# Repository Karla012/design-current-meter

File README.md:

# Diseño de un Sistema de Medición de Corriente para Microcontroladores con Transmisión Inalámbrica

### Autores
- **Karla Vanessa Ruíz González** — Universidad Industrial de Santander  
- **Óscar Andrés Meza Ortiz** — Universidad Industrial de Santander  

---

## Descripción del Proyecto

Este proyecto tiene como objetivo el diseño de un sistema electrónico operado por batería, que permita medir la corriente de operación de un microcontrolador en sus distintos modos de funcionamiento: modo normal y modo de sueño profundo. La medición se realiza de forma periódica, alternando entre ambos modos, lo que permite analizar el comportamiento energético del microcontrolador a lo largo del tiempo.

El sistema está diseñado para ofrecer precisión y bajo burden voltage en la medición, permitiendo detectar corrientes tanto en el orden de los miliamperios como de los microamperios. Para ello, se implementa un sistema de cambio de rango (manual o automático) que adapta la medición al nivel de corriente detectado. La señal medida es amplificada y enviada a un conversor analógico-digital, y finalmente, los datos se transmiten inalámbricamente a través de un microcontrolador ESP32.

---

## Estructura del Repositorio

- `docs/` – Informe final y presentación del proyecto.
- `hardware/` – Esquemáticos y diseño de PCB del circuito.
- `firmware/` – Código del microcontrolador para la transmisión inalámbrica.
- `simulacion/` – Resultados y archivos de simulaciones.
- `app_inventor/` – Archivos del diseño de la app móvil para visualizar los datos.

---

## Transmisión de Datos

El sistema emplea un ESP32 para la transmisión inalámbrica de las mediciones. Estas son recibidas por una aplicación desarrollada en [App Inventor](https://appinventor.mit.edu/), permitiendo visualizar en tiempo real el comportamiento de la corriente en el microcontrolador evaluado.

---

## Estado del Proyecto

Este trabajo corresponde al diseño completo y simulado del sistema de medición. No se realizó una implementación física, pero se desarrollaron y documentaron todos los bloques funcionales, respaldados por simulaciones, selección de componentes y diseño de una aplicación móvil funcional.

---

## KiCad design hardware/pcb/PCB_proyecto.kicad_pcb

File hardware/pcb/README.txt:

Contiene los archivos del diseño de la PCB para fabricación.

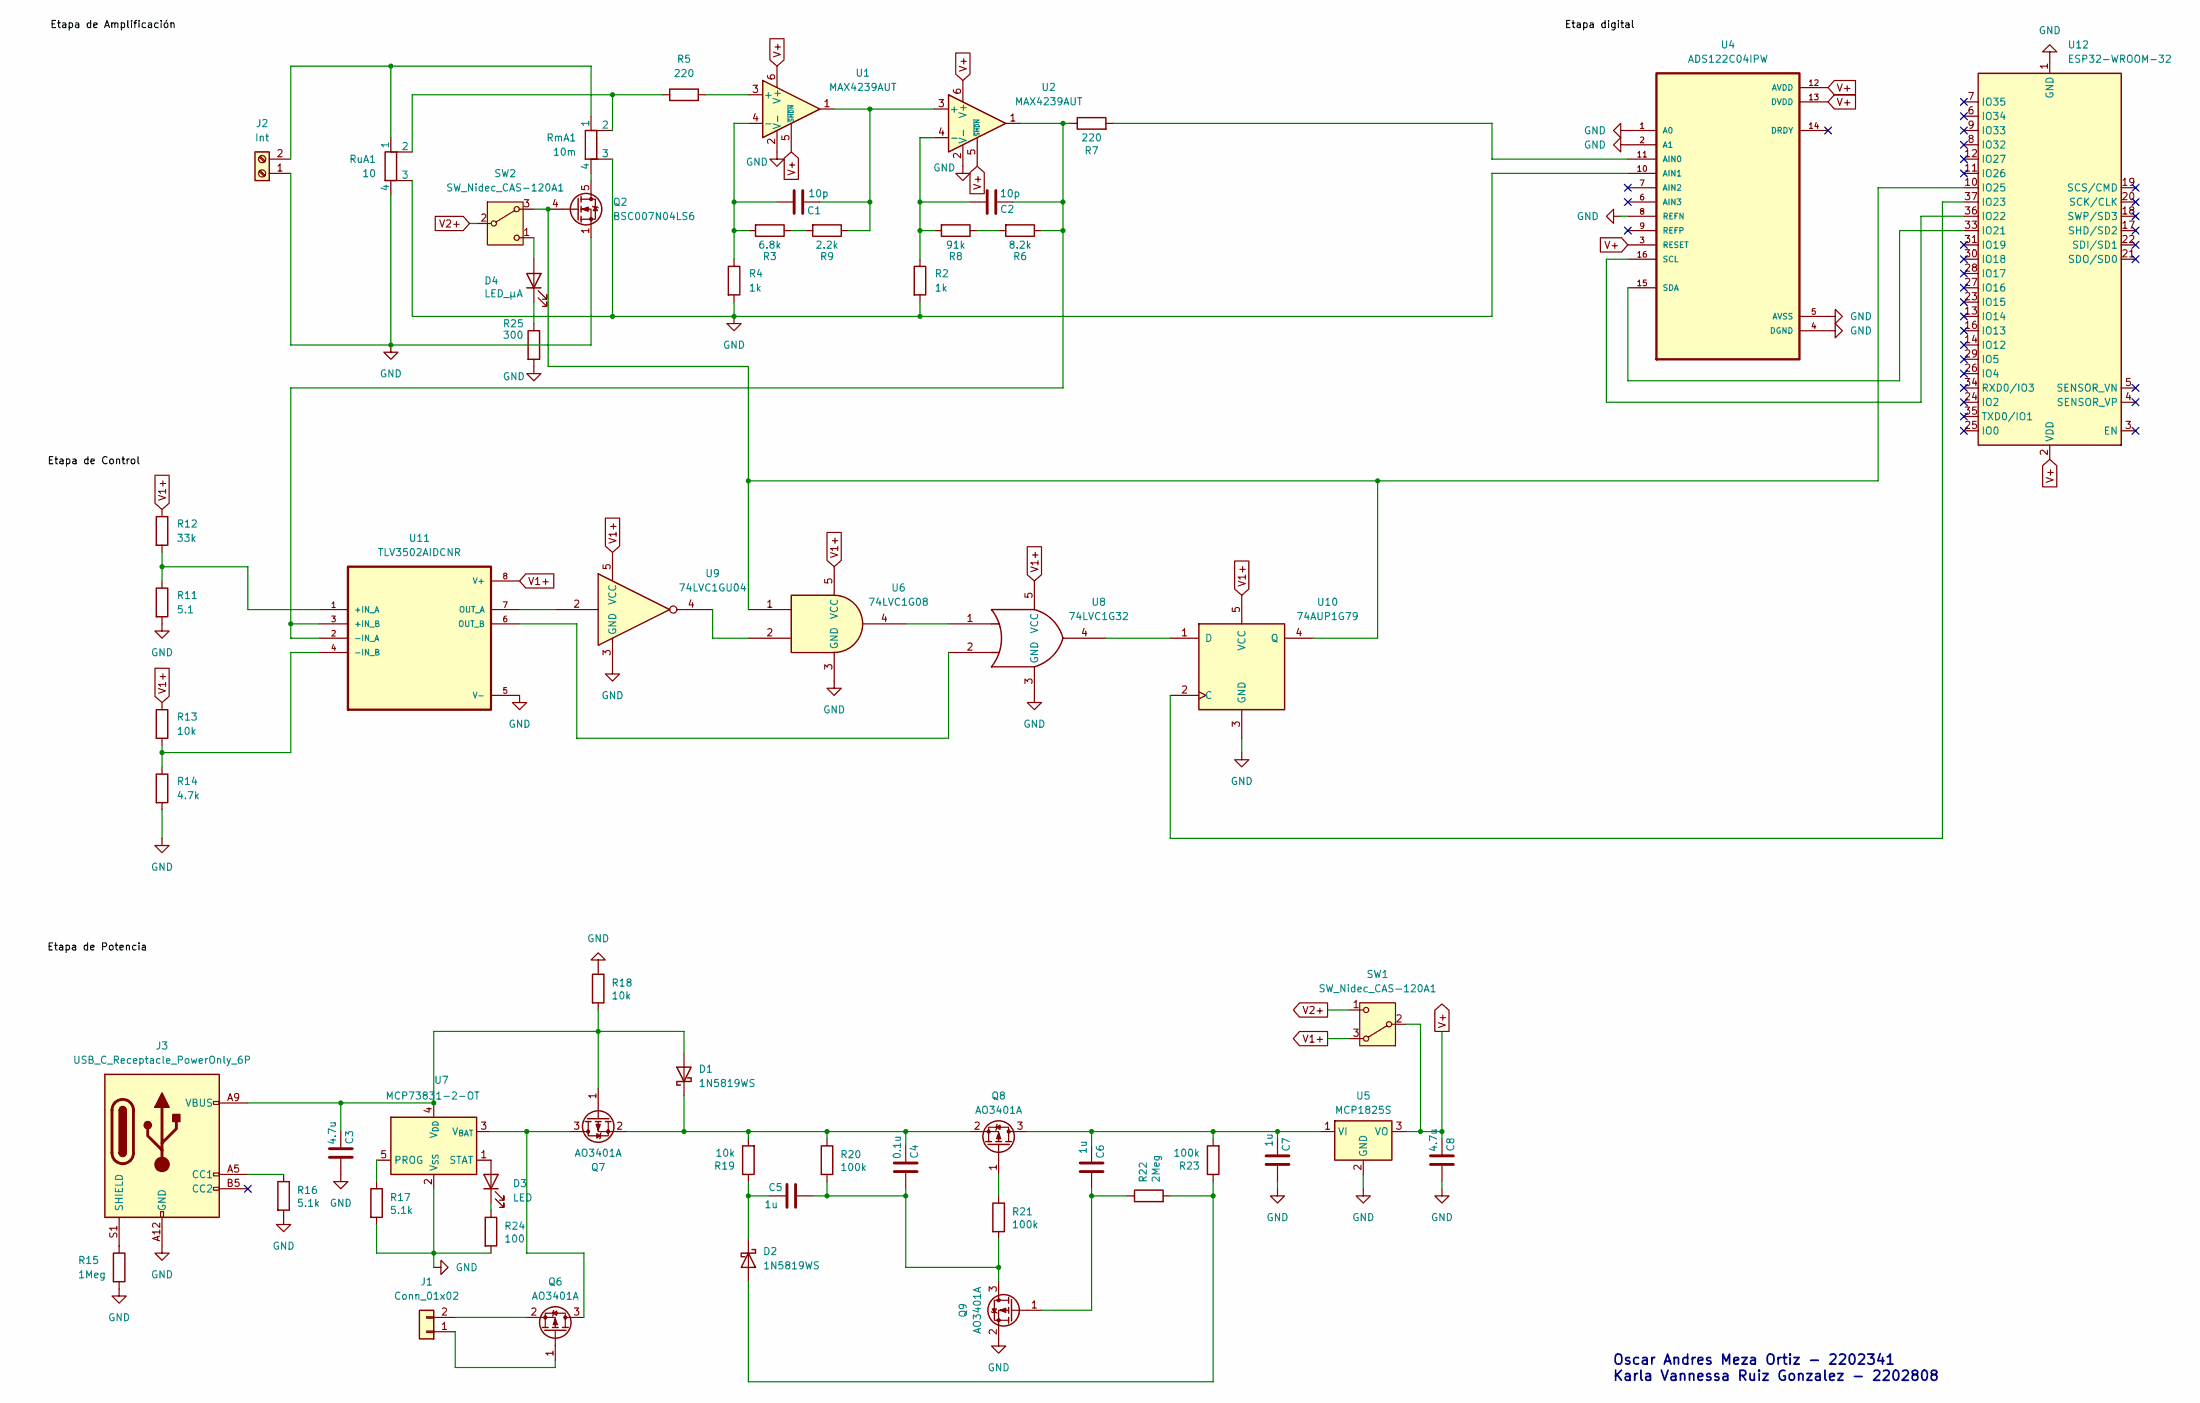
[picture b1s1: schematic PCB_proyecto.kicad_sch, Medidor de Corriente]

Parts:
C1, C2: 10p; C_0201_0603Metric
C3, C8: 4.7u; C_0201_0603Metric
C4: 0.1u; C_0201_0603Metric
C5, C6, C7: 1u; C_0201_0603Metric
D1, D2: 1N5819WS; D_SOD-323
D3: LED; LED_0402_1005Metric
D4: LED_µA; LED_0402_1005Metric
J1: Conn_01x02; JST_PH_B2B-PH-K_1x02_P2.00mm_Vertical
J2: Int; TerminalBlock_Phoenix_MKDS-3-2-5.08_1x02_P5.08mm_Horizontal
J3: USB_C_Receptacle_PowerOnly_6P; USB_C_Receptacle_GCT_USB4125-xx-x-0190_6P_TopMnt_Horizontal
Q2: BSC007N04LS6; TDSON-8-1
Q6, Q7, Q8, Q9: AO3401A; SOT-23
R2, R4: 1k; R_1206_3216Metric
R3: 6.8k; R_1206_3216Metric
R5: 220; R_1206_3216Metric_Pad1.30x1.75mm_HandSolder
R6: 8.2k; R_1206_3216Metric
R7: 220; R_1206_3216Metric
R8: 91k; R_1206_3216Metric
R9: 2.2k; R_1206_3216Metric
R11: 5.1; R_1206_3216Metric
R12: 33k; R_1206_3216Metric
R13, R18, R19: 10k; R_1206_3216Metric
R14: 4.7k; R_1206_3216Metric
R15: 1Meg; R_1206_3216Metric
R16, R17: 5.1k; R_1206_3216Metric
R20, R21, R23: 100k; R_1206_3216Metric
R22: 2Meg; R_1206_3216Metric
R24: 100; R_1206_3216Metric
R25: 300; R_1206_3216Metric
RmA1: 10m; R_Shunt_Vishay_WSKW0612
RuA1: 10; R_Shunt_Vishay_WSKW0612
SW1, SW2: SW_Nidec_CAS-120A1; Nidec_Copal_CAS-120A
U1, U2: MAX4239AUT; SOT-23-6
U4: ADS122C04IPW; SOP65P640X120-16N
U5: MCP1825S; SOT-323_SC-70
U6: 74LVC1G08; SOT-23-5
U7: MCP73831-2-OT; SOT-23-5
U8: 74LVC1G32; SOT-23-5
U9: 74LVC1GU04; SOT-143R
U10: 74AUP1G79; SOT-353_SC-70-5
U11: TLV3502AIDCNR; SOT65P280X145-8N
U12: ESP32-WROOM-32

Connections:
GND: C3.1, C7.1, C8.1, J2.1, J3.A12 (GND), J3.B12 (GND), Q2.1 (S), Q2.2 (S), Q2.3 (S), Q9.2 (S), R2.2, R4.2, R11.2, R14.2, R15.2, R16.2, R17.2, R18.1, R24.2, R25.2, RmA1.3, RuA1.3, RuA1.4, U1.2 (V-), U2.2 (V-), U4.1 (A0), U4.2 (A1), U4.4 (DGND), U4.5 (AVSS), U4.8 (REFN), U4.10 (AIN1), U5.2 (GND), U6.3 (GND), U7.2 (V_{SS}), U8.3 (GND), U9.3 (GND), U10.3 (GND), U11.5 (V-), U12.1 (GND), U12.15 (GND), U12.38 (GND), U12.39 (GND); also elsewhere on the board
unnamed: C3.2, D1.2 (A), J3.A9 (VBUS), J3.B9 (VBUS), Q7.1 (G), R18.2, U7.4 (V_{DD})
unnamed: C4.2, D1.1 (K), Q7.2 (S), Q8.2 (S), R19.2, R20.1
unnamed: D2.2 (A), R22.2, R23.1
unnamed: C5.2, D2.1 (K), R19.1
unnamed: D3.2 (A), U7.1 (STAT)
unnamed: D3.1 (K), R24.1
unnamed: D4.2 (A), SW2.1 (C)
unnamed: D4.1 (K), R25.1
unnamed: J1.1, Q6.1 (G)
unnamed: J1.2, Q6.2 (S)
unnamed: J2.2, RmA1.1, RuA1.1
unnamed: J3.A5 (CC1), R16.1
unnamed: J3.S1 (SHIELD), R15.1
unnamed: Q2.5 (D), RmA1.4
unnamed: Q2.4 (G), SW2.3 (A), U6.1, U10.4 (Q), U12.10 (IO25)
unnamed: Q6.3 (D), Q7.3 (D), U7.3 (V_{BAT})
unnamed 17: C6.2, C7.2, Q8.3 (D), R23.2, U5.1 (VI); also elsewhere on the board
unnamed: Q8.1 (G), R21.1
unnamed: C4.1, C5.1, Q9.3 (D), R20.2, R21.2
unnamed: C6.1, Q9.1 (G), R22.1
unnamed: R3.1, R9.2
unnamed: R5.1, RmA1.2, RuA1.2
unnamed: R6.2, R8.1
unnamed: R5.2, U1.3 (+)
unnamed: C1.1, R3.2, R4.1, U1.4 (-)
unnamed: C1.2, R9.1, U1.1, U2.3 (+)
unnamed: C2.1, R2.1, R8.2, U2.4 (-)
unnamed: R7.2, U4.11 (AIN0)
unnamed: U6.2, U9.4
unnamed: U6.4, U8.1
unnamed: R17.1, U7.5 (PROG)
unnamed: U10.2 (C), U12.37 (IO23)
unnamed: U8.4, U10.1 (D)
unnamed: R11.1, R12.2, U11.1 (+IN_A)
unnamed: C2.2, R6.1, R7.1, U2.1, U11.2 (-IN_A), U11.3 (+IN_B)
unnamed: R13.2, R14.1, U11.4 (-IN_B)
unnamed: U9.2, U11.7 (OUT_A)
unnamed: U8.2, U11.6 (OUT_B)
unnamed: U4.15 (SDA), U12.33 (IO21)
unnamed: U4.16 (SCL), U12.36 (IO22)
V1+: R12.1, R13.1, SW1.3 (A), U6.5 (VCC), U8.5 (VCC), U9.1, U9.5 (VCC), U10.5 (VCC), U11.8 (V+)
V2+: SW1.1 (C), SW2.2 (B)
V+: C8.2, SW1.2 (B), U1.5 (~SHDN), U1.6 (V+), U2.5 (~SHDN), U2.6 (V+), U4.3 (RESET), U4.12 (AVDD), U4.13 (DVDD), U5.3 (VO), U12.2 (VDD); also elsewhere on the board

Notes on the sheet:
Oscar Andres Meza Ortiz - 2202341 Karla Vannessa Ruiz Gonzalez - 2202808

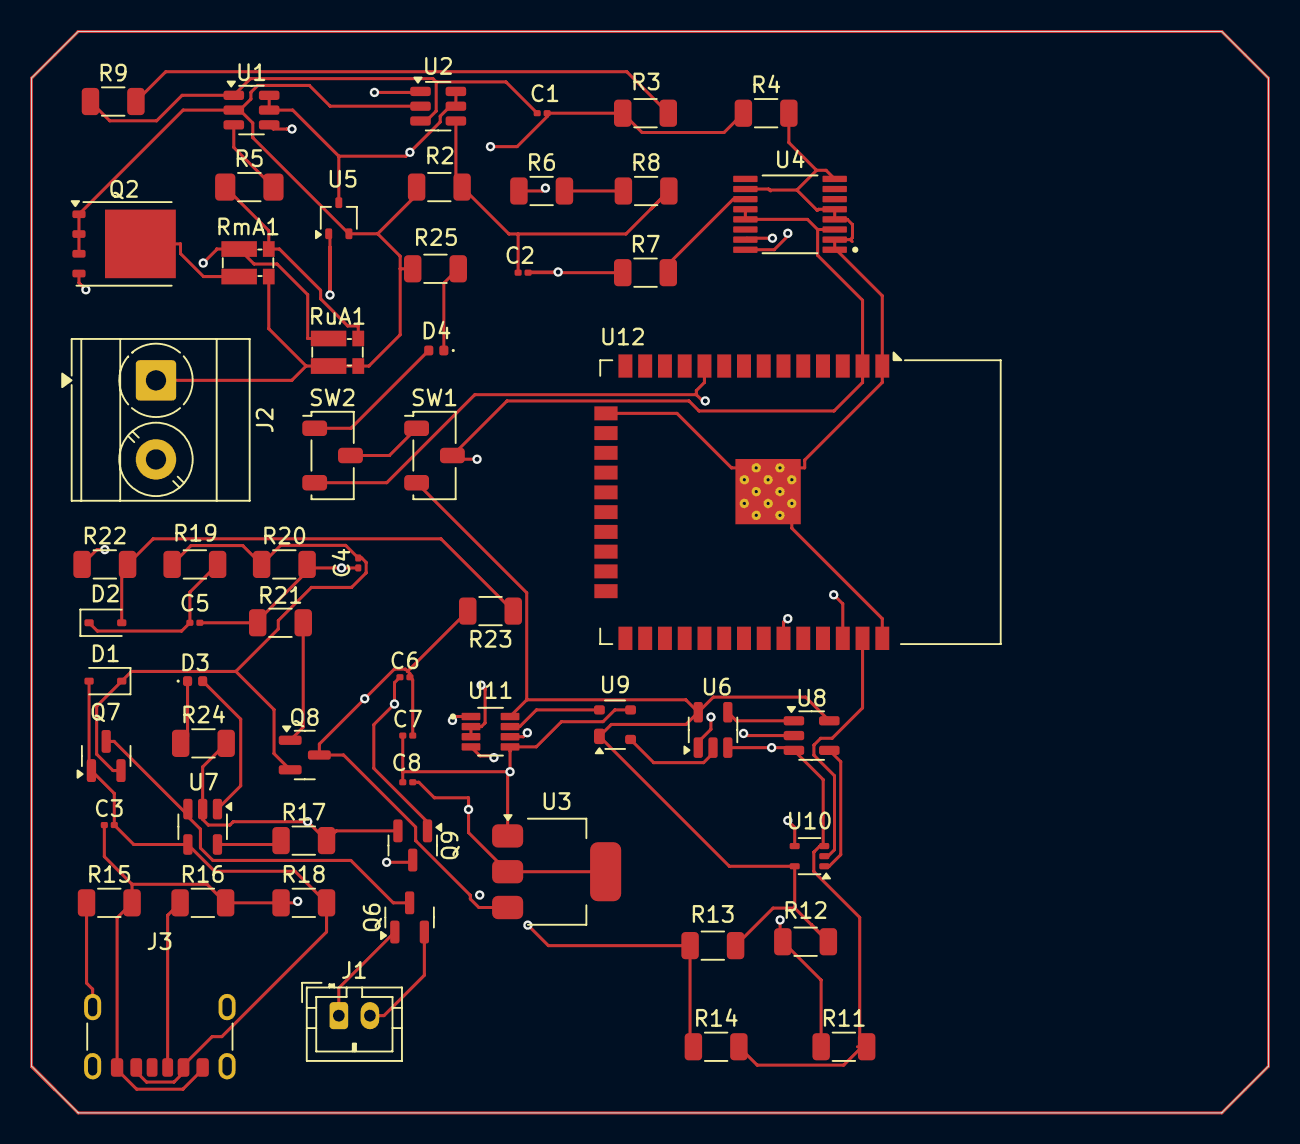
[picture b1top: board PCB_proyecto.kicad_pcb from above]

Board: 4 copper layers, 79.5 x 69.5 mm, 59 parts (0 on the bottom side), 44 nets.

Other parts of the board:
U3: AMS1117-3.3; SOT-223-3_TabPin2

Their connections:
GND: U3.1 (GND); also elsewhere on the board
unnamed 17: U3.3 (VI); also elsewhere on the board
V+: U3.2 (VO); also elsewhere on the board

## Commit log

2025-04-19 Archivo fuente
2025-04-19 Versión instalable
2025-04-19 update app
2025-04-19 update codigo
